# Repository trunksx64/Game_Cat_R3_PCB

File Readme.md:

# Game//Cat ::: Revsion_R3 :: Versión 2.91

## Razon de Ser e Inspiración

Este Control se basa en la Idea Original del Game//Cat Version R1, el cual asu vez se inspira en el diseño del joystick y botones del Arduino Esplora. El primer Control se implemento para ser usado como parametrizador y las siguientes revsiones se presento como Tesis de Grado de Especialización de Instrumentación Industrial que curse. Se Utilizo principalmente como Herramienta de Programacion para Tarjeta de Control de Ascensores Usando Un Firmware de Codigo Cerrado. Se Implemento FREERTOS para su uso, asi como librerias Basicas en MplabX y XC16. La idea principal es usar los Microcontroladores de 16Bits de Microchip con perifericos listos y configurados. Es pequeño y Portable, ideal para llevar a todo lado, no intenta competir con controles similares a Arduino. Se desea implentar a futuro un Bootloader tanto por USB, RS232, SD y CAN.

Por el Momento Requiere Programdor Basado en Pickit2 como minimo o un ICD3. Link

## Caracteristicas del Hardware

  * Microcontrolador PIC24HJ128GP504.
  * Pantalla LCD PCD8544 (Based Nokia GLCD) - SPI.
  * Joystick Análogo de 2 ejes + Botón Digital.
  * 4 Botones Digitales.
  * Accelerometro - MMA8452Q - I2C. 
  * Sensor de Temperatura (LM61).
  * Sensor de Luz (LDR).
  * Memoria Eeprom 24LCXXX - I2C.
  * Memoria Ram 23KXX - SPI.
  * Ranura Memoria Micro-SD - SPI.
  * Buzzer por PWM.
  * Conexión USB - FTDI-RL232/UART - 5V.
  * Conexión CAN 5V.
  * 2 LED´s de Actividad.
  * Salidas Para PWM y UART - Configurables - 3V.
  * Conexión ICSP con linea AUX, para control extra de puerto.
  * Cargador de Bateria Lipo (MCP73831) con Indicador LED.

## Caracteristicas Espesificas

  * Debido a que el PIC trabaja a 3.3V, el uso del MCP2551 y el FTDI-RL232 esta a 5V, alimentado directamente por el Control USB, el FTDI-RL232 se encarga de "gestionar" la alimentación del sistema proporcionando un arranque suave en la tensión, luego se pasa por un regulador de 3,3V para alimentar el resto de componentes.
  * Para Potabilidad he agregado un control para la carga de Baterías de tipo Lipo, este gobernado el con el CI MCP73831, el cual mediante el uso del Mosfet DMP1045, intercambia la alimentación proveniente del FTDI-RL232 y la Batería según el estado de conexión USB, se puede usar Baterías de 3,7V en adelante hasta un máximo de 6V, cuando el Game//Cat esta usando la Batería, el FTDI-RL232 se deshabilita.
  * Para el Manejo del Joystick, Botones, Sensor de Temperatura y Luz. he usado el CI-74HC4051, que es un Multiplexor Análogo para leer los Valores por el Modulo ADC, el cual puede usarse de 10 o 12Bits en conjunto con un canal DMA si fuere necesario.
  * La Comunicación UART, es una Salida/Entrada dedicada con un conversor de tensión de 3.3V a 5V de forma bidireccional con trasnsitores Mosfet, con el fin de proteger y poder comunicar el PIC24H con cualquier tipo de dispositivo.
  * La Comunicación USB se hace por medio del CI FTDI-RL232, esto es porque el PIC no posee dicho Modulo y ademas permite ahorrar en la Memoria del PIC el Stack del USB, esto permite que sea Conectar y Usar, puesto que los Drives de este USB son reconocidos de forma inmediata por Windows y Linux sin problemas.
  * La Comunicación CAN la he Incluido porque en estos momentos trabajo con esta interface y su popularidad ha crecido bastante, por experiencia este BUS es muy robusto y fácil de usar, en el PIC se hace uso de dos canales DMA teniendo una respuesta bastante rápida y sin sacrificar la memoria RAM principal, su conexión se hace por medio del Transeiver MCP2551, ademas he agregado un par de diodos TVH para proteger dicho CI.
  * La Ranura para la Tarjeta Micro-SD, posee conexión Modulo SPI la cual esta compartida con la Memoria Ram 23Kxxx, Ademas la pantalla posee también una conexión al segundo Modulo SPI, que puede usarse para "colgar" otros dispositivos si no vamos ha usar la Pantalla.
  * El control del Buzzer se ha dejado por un Pin que puede ser usado tanto por el Modulo PWM o un pin Común, su uso dependerá del Programa o Aplicación.
  * Posee una Memoria I2C en conjunto con un Accelerometro, con comunicación directa.
  * La programación se hace por medio de la conexión ICSP o Bootloader por USB, usando cualquier programador, PICKIT2-3 y/ó ICD2-3, igual estas salidas pueden usarse como cualquier puerto, teniendo presente que no poseen ninguna protección a tensiones superiores de 3,3V.
  * Ya por Ultimo, he dejado dos visualizadores, que son libres de uso.

Básicamente esto es el GAME//CAT, una tarjeta mas que un sistema de control para usuarios avanzados, es una tarjeta de entrenamiento para los principiantes, puesto que todo lo que incluye hace uso forzoso de todo los controles que el PIC24HJ128GP504 incorpora.

## Microcontrolador

* Architecture 16-bit.
* CPU Speed Max. 40 MIPS.
* Memory Type Flash.
* Program Memory 128Kb.
* RAM 8,192 Bytes.
* Temperature Range C -40 to 150.
* Operating Voltage Range (V) 3 to 3.6.
* I/O Pins 35 & Pin Count    44.
* Internal Oscillator 7.37 MHz, 32.768 kH.
* Digital Communication Peripherals 2-UART, 2-SPI,1-I2C, 1-CAN.
* Comparators 2, Capture/Compare/PWM Peripherals 4/4, PWM Resolution bits 16.
* Timers 5 x 16-bit 2 x 32-bit.
* Parallel Port PMP(No Usado), Hardware RTCC-1 (No Usado).
* Chanel DMA-8.
* Cap Touch Channels-13 (No Usado).

## Versiones

* 2017 : 1.0.0 : Primera Version en Kicad 4
* 2017 : 1.2.0 : Se Agrego Conversion de Tension 5V a 3.3V Bidirecional en salida UART y PWM, se elimino conexion DC externa.
* 2018 : 2.0.0 : Se Migro completamente a Kicad 5, el Led control se removio para dar opcion de seleccion de Periferico SPI (Ram y SD).
* 2018 : 2.1.0 : Se rediseño y corrigio error en boton del Joystick, se corrigio el trucado de lineas de Programacion PGM y PGD.
* 2018 : 2.2.0 : Se Agrego Resistencias de proteccion (0Ohm) en entradas Jack RJ11 de Programacion.
* 2018 : 2.1.0 : Se Agrego y Calibro Resistencia del Boton de Reset, se agrego control se Carga para Bateria Lipo 3.3V.
* 2018 : 2.5.0 : Se Actulizaron Logos de la Marca y de Hardware Libre, se Actulizo a licencia Creative Commons V4.
* 2018 : 2.7.0 : Se Actulizaron las Librerias de Modulos de Kicad, basadas en Progetti.
* 2018 : 2.9.0 : Se Agregaron condensadores de filtrado al multiplexor analogo, se cambiaron los botones por diseño con poste.
* 2019 : 2.9.1 : Se Organizaron los Archivos para Hospedarlos en Github, Se Ordenaron condensandores y Cristal del PIC.

## Creditos

xDNA Electronics & Desing es una Micro-empresa Personal, que se dedica y encarga de elaborar proyectos de Control y Automatización por pedido, su idea es colaborar y ayudar a quines a si lo requieran, el proyecto se hizo principalmente como Hobby el cual gracias a terceros se pudo implementar y hacer su creación, por lo cual se da la libertad de usarlo para experimentar sin hacer uso comercial del mismo.

## Licencia

Licensed under Attribution-NonCommercial-ShareAlike 4.0 International (CC BY-NC-SA 4.0)

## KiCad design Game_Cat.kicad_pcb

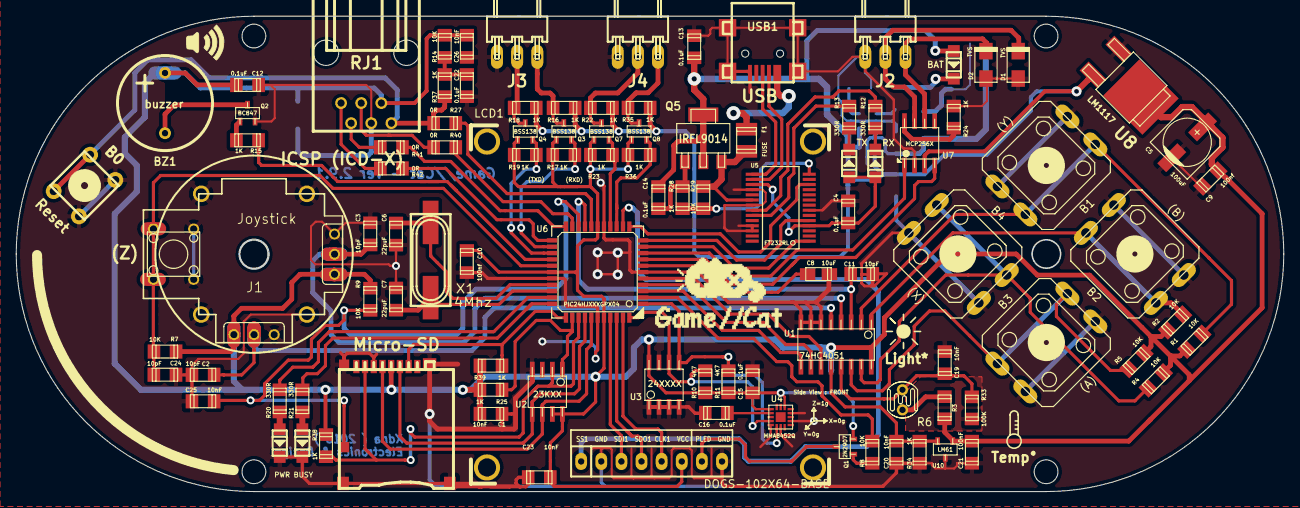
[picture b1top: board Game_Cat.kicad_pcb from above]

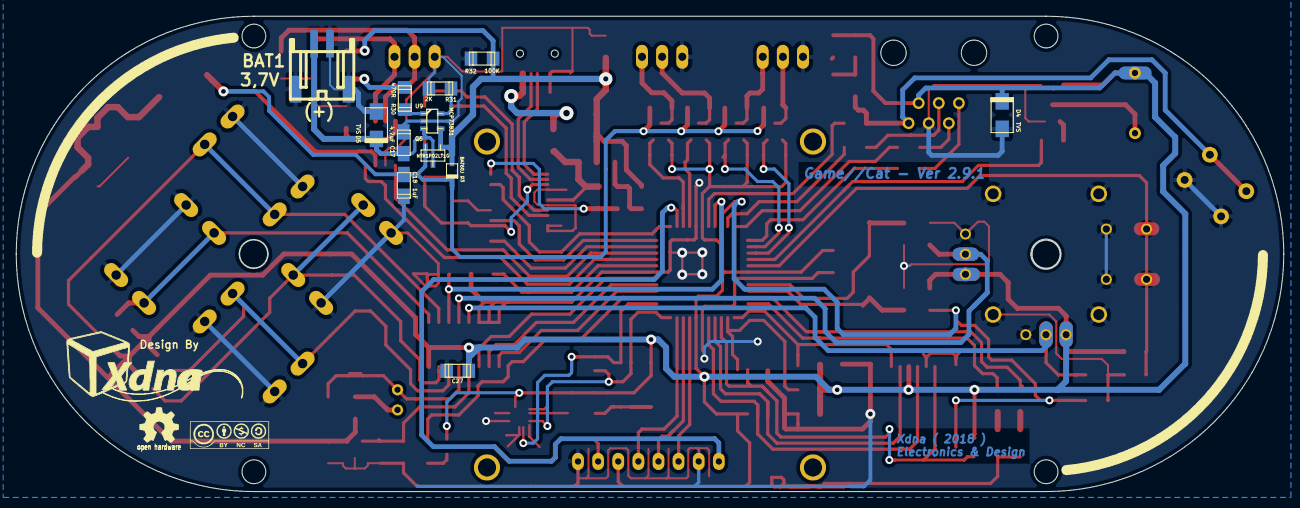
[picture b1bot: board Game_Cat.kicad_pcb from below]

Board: 2 copper layers, 160.0 x 60.0 mm, 113 parts (12 on the bottom side), 84 nets.

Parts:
B0: Reset; PCB_PUSH
B1: (Y); tactil-swicht-post-yellow-12x12
B2: (B); tactil-swicht-post-red-12x12
B3: (A); tactil-swicht-post-green-12x12
B4: (X); tactil-swicht-post-blue-12x12
BAT1: 3,7V; s2b-ph-sm4-tb
BZ1: buzzer; buzzer_tmb
C1, C19, C20, C23, C25, C26: 10nF; c_1206
C2, C3, C11, C24: 10pF; c_1206
C4, C12, C13, C14, C15, C16, C22: 0.1uF; c_1206
C5: 100uF; c_elec_6.3x4.5
C6, C7: 22puF; c_1206
C8: 10uF; c_tant_S
C9, C10: 100nf; c_1206
C17: 4,7uF; c_tant_A
C18: 1uF; c_tant_A
C21: 100nF; c_1206
C27: 1uF; c_1206
D1, D2, D4, D5: TVS; do214ac
D3: BAT60J; sod323
F1: FUSE; r_1210
J1: Joystick; joystick
J2: CAN; molex-7593-3
J3: UART; molex-7593-3
J4: PWM; molex-7593-3
LCD1: DOGS-102X64-BASE; lcd-dogs-102x64-base
LD1: RX; Led_1206
LD2: TX; Led_1206
LD3: PWR; Led_1206
LD4: BUSY; Led_1206
LD5: BAT; Led_1206
Q1: 2N2907; sot23
Q2: BC847; sot23
Q3, Q4, Q7, Q8: BSS138; sot23
Q5: IRFL9014; sot223
Q6: NTR1P02LT1G; sot23
R1, R2, R3, R4, R5, R7, R8, R9, R14, R29: 10K; r_1206
R6: LDR; photo-cell
R10, R11: 4K7; r_1206
R12, R13, R20, R21: 330R; r_1206
R15, R16, R17, R18, R19, R22, R23, R24, R25, R28, R34, R35, R36, R37, R38, R39: 1K; r_1206
R27, R40, R41, R42: 0R; r_1206
R30: 470R; r_1206
R31: 2K; r_1206
R32, R33: 100K; r_1206
RJ1: ICSP (ICD-X); molex_6p6c
SD1: Micro-SD; micro-sd-socket
U1: 74HC4051; so-16
U2: 23KXX; so-8
U3: 24XXXX; so-8
U4: MMA8452Q; qfn-16
U5: FT232RL; ssop-28
U6: PIC24HJXXXGPX04; lqfp44
U7: MCP256X; psop-8
U8: LM1117; d-pak
U9: MCP73831; sot23-5
U10: LM61; sot23
USB1: USB; conn_usb_B_mini_smd
X1: 4Mhz; hc-49_smd

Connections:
+3V3: BZ1.1, C1.1, C5.1, C9.1, C10.1, C12.1, C15.1, C21.1, C23.1, C26.1, C27.2, D4.2, J1.1, J1.4, LCD1.6, Q1.3, Q3.1, Q4.1, Q7.1, Q8.1, R1.1, R2.1, R3.1, R4.1, R5.1, R7.2, R9.2, R10.1, R11.1, R14.1, R17.1, R19.1, R23.1, R25.2, R36.1, R38.2, R39.2, RJ1.2, SD1.4, U1.16, U2.7, U2.8, U3.8, U4.1, U4.14, U6.17, U6.28, U6.40, U8.2, U10.1
+5C: C18.1, D3.2, Q6.3, R16.1, R18.1, R22.1, R35.1, U7.3, U8.3
/B(A): B3.1, B3.2, R5.2, U1.14
/B(B): B2.1, B2.2, R2.2, U1.1
/B(X): B4.1, B4.2, R4.2, U1.15
/B(Y): B1.1, B1.2, R1.2, U1.2
/BAT: BAT1.1, C17.1, D5.2, Q6.2, U9.3
/CANH: D1.2, J2.2, U7.7
/CANL: D2.2, J2.1, U7.6
/CBUS0: R13.2, U5.23
/CBUS1: R12.2, U5.22
/CTRL: BZ1.2, Q2.2
/LED: LCD1.7, Q1.2
/PROG: R31.2, U9.5
/RESET_: R27.1, U6.18
/RS: R24.1, U7.8
/USBDM: U5.16, USB1.2
/USBDP: U5.15, USB1.3
/VCAP: C8.1, U6.7
/_AUX: R42.1, RJ1.6
/_PGC: R41.1, RJ1.5
/_PGD: R40.1, RJ1.4
ADC-0: C11.2, U1.3, U6.19
AUX: R42.2, U6.23
AXIS(X): C2.1, J1.2, U1.5
AXIS(Y): C3.1, J1.5, U1.4
BUTTON-R: C24.1, J1.7, R7.1, U6.27
BUZZER: R15.1, U6.26
CHECK-SD: C25.1, R9.1, SD1.CD2, U6.20
CLK1: LCD1.5, U6.43
CLK2: SD1.5, U2.6, U6.38
CTRL-LED: R8.2, U6.2
GND: B0.1, B0.3, B1.3, B1.4, B2.3, B2.4, B3.3, B3.4, B4.3, B4.4, BAT1.2, C1.2, C2.2, C3.2, C4.2, C5.2, C6.2, C7.2, C8.2, C9.2, C10.2, C11.1, C12.2, C13.2, C15.2, C16.2, C17.2, C18.2, C19.2, C20.2, C21.2, C22.2, C23.2, C24.2, C25.2, C26.2, C27.1, D1.1, D2.1, D4.1, D5.1, J1.3, J1.6, J1.8, J1.9, J2.3, J3.3, J4.3, LCD1.2, LCD1.8, LD3.2, LD4.2, Q2.3, R24.2, R31.1, R32.1, R33.2, R34.2, RJ1.3, SD1.6, SD1.CD1, U1.6, U1.7, U1.8, U2.4, U3.1, U3.2, U3.3, U3.4, U3.7, U4.5, U4.7, U4.10, U4.12, U5.7, U5.18, U5.21, U5.25, U5.26, U6.6, U6.16, U6.29, U6.39, U7.2, U8.1, U9.2, U10.2, USB1.5
LED-BUSY: R21.2, U6.33
LED-PW: R20.2, U6.32
LIGHT: C19.1, R6.2, R33.1, U1.13
LV: C4.1, LD1.1, LD2.1, U5.4, U5.17
MUX-A: U1.11, U6.5
MUX-B: U1.10, U6.4
MUX-C: U1.9, U6.3
unnamed: C13.1, C14.2, D3.1, LD5.1, Q5.2, Q6.1, R32.2, U9.4
unnamed: C14.1, Q5.1, R28.2
unnamed: C16.1, U4.2
unnamed: C22.1, R14.2, R37.1
unnamed: F1.1, USB1.1
unnamed: LD1.2, R12.1
unnamed: LD2.2, R13.1
unnamed: LD3.1, R20.1
unnamed: LD4.1, R21.1
unnamed: LD5.2, R30.1
unnamed: Q1.1, R8.1
unnamed: Q2.1, R15.2
unnamed: R3.2, R6.1
unnamed: R30.2, U9.1
OSC1: C6.1, U6.30, X1.1
OSC2: C7.1, U6.31, X1.2
PGC: R41.2, U6.22
PGD: R40.2, U6.21
PWMA-3V3: Q7.3, R23.2, U6.15
PWMA-5V: J4.2, Q7.2, R22.2
PWMB-3V3: Q8.3, R36.2, U6.14
PWMB-5V: J4.1, Q8.2, R35.2
PWREN: R28.1, R29.2, U5.14
RESET: B0.2, B0.4, R27.2, R37.2, RJ1.1
RXC: U6.8, U7.4
RXD: U5.5, U6.11
RXU-3V3: Q4.3, R19.2, U6.25
RXU-5V: J3.2, Q4.2, R18.2
SCL: R10.2, U3.6, U4.4, U6.44
SDA: R11.2, U3.5, U4.6, U6.1
SDI1: LCD1.3, U6.41
SDI2: R38.1, SD1.7, U2.2, U6.36
SDO1: LCD1.4, U6.42
SDO2: SD1.3, U2.5, U6.37
SLEEP: U5.12, U6.12
SS1: LCD1.1, U6.13
SS_RAM: R25.1, U2.1, U6.35
SS_SD: R39.1, SD1.2, U6.34
TEMP: C20.1, R34.1, U1.12, U10.3
TXC: U6.9, U7.1
TXD: U5.1, U6.10
TXU-3V3: Q3.3, R17.2, U6.24
TXU-5V: J3.1, Q3.2, R16.2
VCC+: F1.2, Q5.3, R29.1, U5.19, U5.20

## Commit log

2020-02-14 Commit inicial
2020-02-14 Set theme jekyll-theme-cayman
